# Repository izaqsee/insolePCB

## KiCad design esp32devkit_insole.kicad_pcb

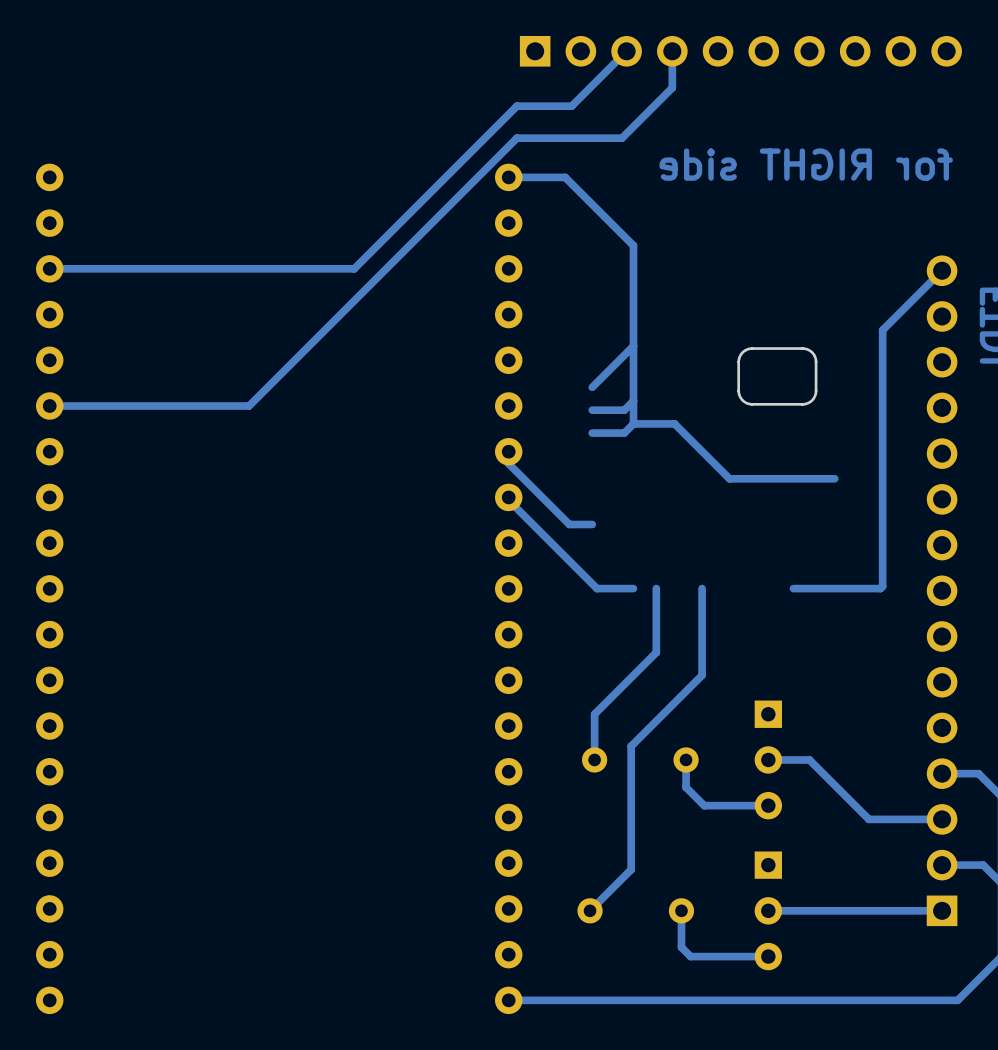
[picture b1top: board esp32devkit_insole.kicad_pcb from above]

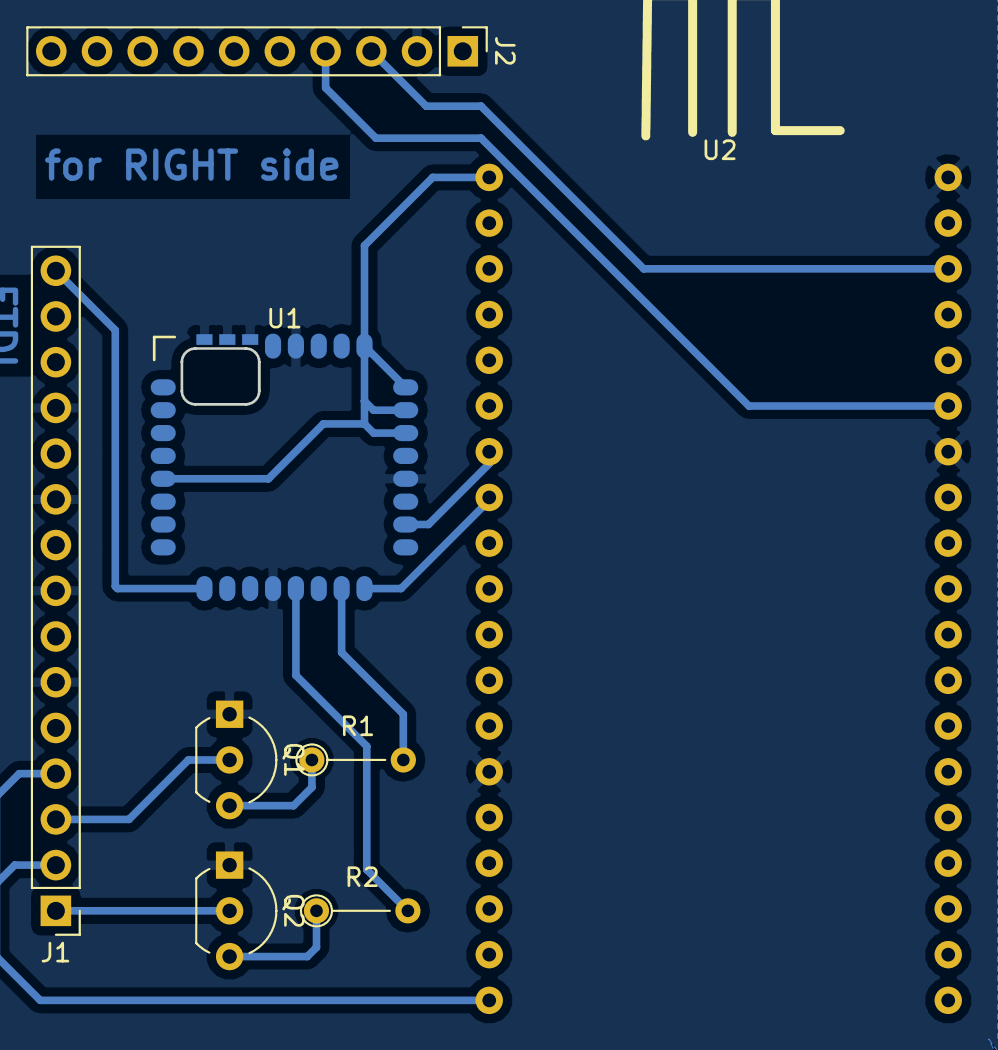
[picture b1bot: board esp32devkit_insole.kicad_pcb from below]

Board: 2 copper layers, 8 parts (8 on the bottom side), 15 nets.

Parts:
J1: Conn_01x15_Female; Socket_Strip_Straight_1x15_Pitch2.54mm
J2: CONN_01x10; Socket_Strip_Straight_1x10_Pitch2.54mm
Q1, Q2: 2SC1815; TO-92_Inline_Wide
R1, R2: R; R_Axial_DIN0204_L3.6mm_D1.6mm_P5.08mm_Vertical
U1: TWE_LITE_SMD; TWE-001L-SMD
U2: ESP32DEVKIT_SOCKET; akitsukiESP32devKITsocket

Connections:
3V3: J1.13, J2.1, U1.5, U1.22, U1.23, U1.24, U1.25, U2.1
+5V: J1.2, J1.4, U2.19
GND: J1.6, J1.8, J1.10, J1.12, J2.2, Q1.1, Q2.1, U1.12, U1.20, U1.28, U1.30, U1.31, U1.32, U2.14, U2.20, U2.26
I018: R2.2, U1.13, U2.28
IO19: R1.2, U1.15, U2.27
IO21: J2.4, U2.25
IO22: J2.3, U2.22
IO32: U1.18, U2.7
IO33: U1.16, U2.8
MFRONT: J1.1, Q2.2
MREAR: J1.3, Q1.2
unnamed: Q1.3, R1.1
unnamed: Q2.3, R2.1
RX: J1.15, U1.9
TX: J1.14, U1.8

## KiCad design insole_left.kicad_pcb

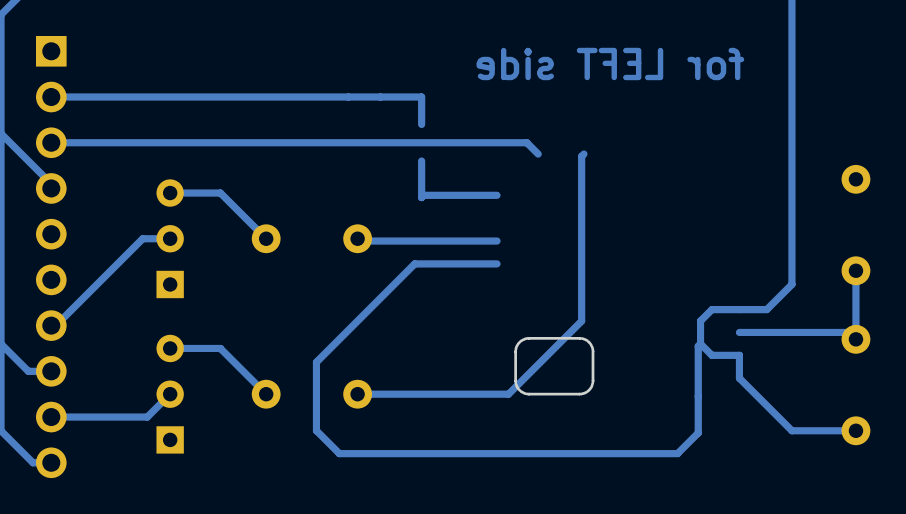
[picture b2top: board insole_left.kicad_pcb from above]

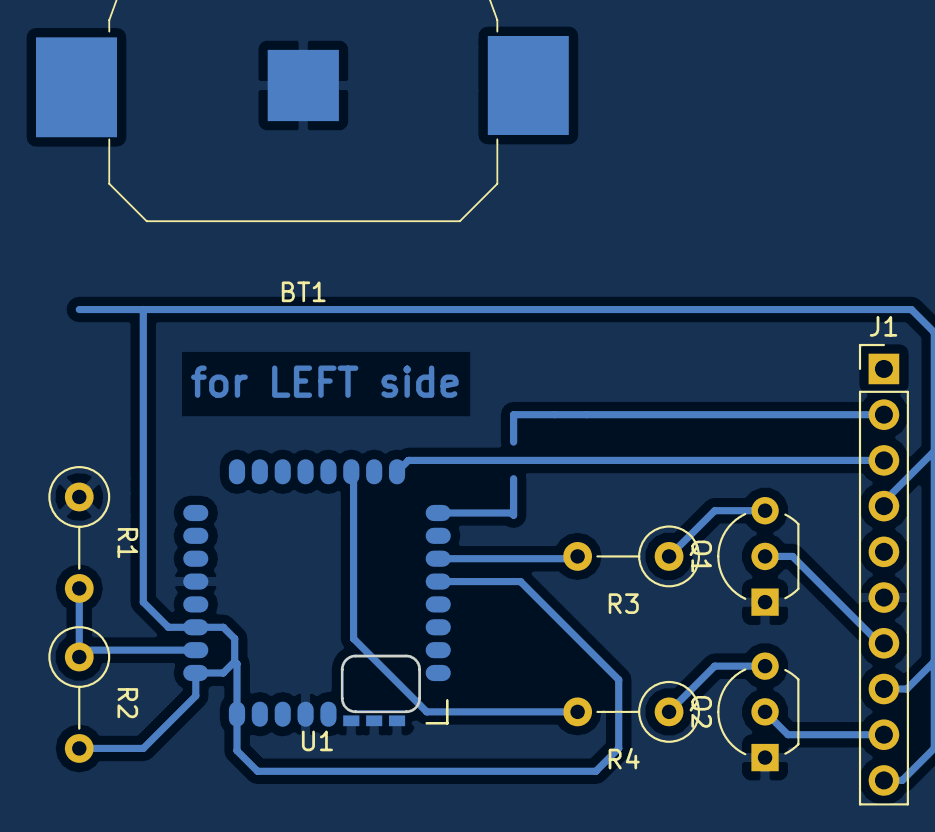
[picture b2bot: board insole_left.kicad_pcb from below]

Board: 2 copper layers, 9 parts (9 on the bottom side), 11 nets.

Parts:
BT1: Battery; Keystone_3034_1x20mm-CoinCell_akizuki
J1: Conn_01x10_Female; Socket_Strip_Straight_1x10_Pitch2.54mm
Q1, Q2: 2SC1815; TO-92_Inline_Wide
R1, R2: 100k; R_Axial_DIN0309_L9.0mm_D3.2mm_P5.08mm_Vertical
R3, R4: 1k; R_Axial_DIN0309_L9.0mm_D3.2mm_P5.08mm_Vertical
U1: TWE_LITE_SMD; TWE-001L-SMD

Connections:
GND: BT1.2, J1.6, Q1.1, Q2.1, R1.1, U1.20, U1.28, U1.30, U1.31, U1.32
unnamed: J1.7, Q1.2
unnamed: J1.9, Q2.2
unnamed: Q1.3, R3.1
unnamed: Q2.3, R4.1
unnamed: R1.2, R2.1, U1.23
unnamed: R3.2, U1.4
unnamed: R4.2, U1.3
RX: J1.3, U1.9
TX: J1.2, U1.8
VCC: J1.4, J1.8, J1.10, R2.2, U1.5, U1.22, U1.24, U1.25
